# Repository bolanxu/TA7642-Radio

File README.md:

# TA7642 Radio

A very tiny pocket AM radio that runs from a single 1.5 V battery. It's a simple, low‑power receiver built around the TA7642 AM demodulator/amplifier IC with a small tuning coil and a coupling transistor to drive headphones. I designed this as a kit and created the PCB in 2021 (a 5th grade project) to learn about radios, basic electronics, and PCB design. More information in the `/docs` folder (The docs were written by me as a 5th grader, don't expect the best english 😅).

## Features
- Pocket‑sized AM radio
- Powered by a single 1.5 V cell (AA/AAA) or possibly a small 1.5V button battery
- TA7642 AM demodulator and amplifier IC
- Tuning via LC tank (coil + variable capacitor)
- Simple output amplifier transistor (Q1) for headphones/earbuds
- Designed as a kit with a compact PCB

## Circuit (overview)
- The LC tank (coil + capacitor) selects the desired AM frequency.  
- The TA7642 performs RF detection (demodulation) and provides a small amount of audio amplification.  
- A single transistor (Q1) follows the TA7642 to raise the audio level enough for headphones or small earbuds.  
- The schematic is shown above (`img/TA7642_radio_sch.png`)..

## Usage
1. Connect a fresh 1.5 V battery (observe polarity).
2. Plug headphones or earbuds into the audio jack or connect to the audio pads.
3. Slowly adjust the ferrite rod in the coil until you hear a station.
4. Fine‑tune the coil/trimmer for best reception and volume.

Note: This radio is optimized for strong local AM stations and will have limited sensitivity compared with larger receivers.

## Tuning and performance tips
- Use low‑impedance earbuds for better volume from the simple output stage.
- If reception is weak, try repositioning the coil or extending an earbud wire as an antenna.
- Small changes in the tuning capacitor or coil turns produce noticeable frequency shifts—tweak gently.
- The TA7642 and a single‑transistor buffer are designed for simplicity and low voltage operation; don't expect the same performance as higher‑powered receivers.

Enjoy building and listening, tiny radios are a great way to learn the fundamentals of RF and analog electronics!

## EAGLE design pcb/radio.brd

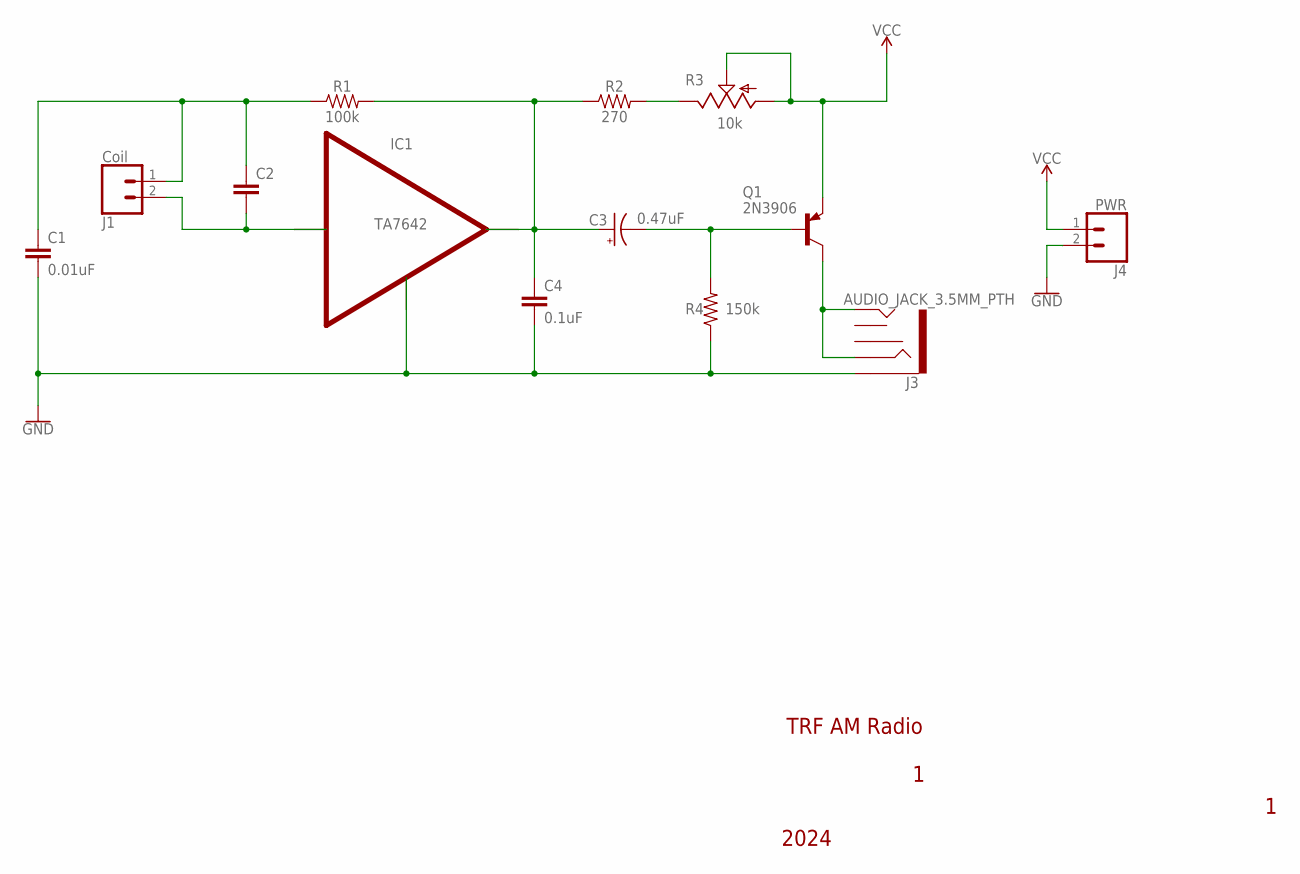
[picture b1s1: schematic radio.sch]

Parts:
C1: 0.01uF; CAP-PTH-2.54
C2: 22PF-PTH-2.54MM-200V-5%; CAP-PTH-2.54
C3: 0.47uF; CPOL-RADIAL-2.5MM-5MM
C4: 0.1uF; CAP-PTH-2.54
IC1: TA7642; TO92
J1: Coil; 1X02
J3: AUDIO_JACK_3.5MM_PTH; AUDIO-JACK
J4: PWR; 1X02
Q1: 2N3906; TO92
R1: 100k; AXIAL-0.3
R2: 270; AXIAL-0.3
R3: 10k; B25P
R4: 150k; AXIAL-0.3

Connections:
GND: C1.2, C4.2, IC1.2 (GND), J3.SLEEVE, J4.2, R4.P$1 (1)
unnamed: J3.RING, J3.TIP, Q1.1 (C)
unnamed: C3.1 (+), C4.1, IC1.1 (OUT), R1.P$2 (2), R2.P$1 (1)
unnamed: C1.1, C2.1, J1.1, R1.P$1 (1)
unnamed: R2.P$2 (2), R3.E
unnamed: C3.2 (-), Q1.2 (B), R4.P$2 (2)
unnamed: C2.2, IC1.3 (INPUT), J1.2
VCC: J4.1, Q1.3 (E), R3.A, R3.S

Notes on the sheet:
TRF AM Radio
2024

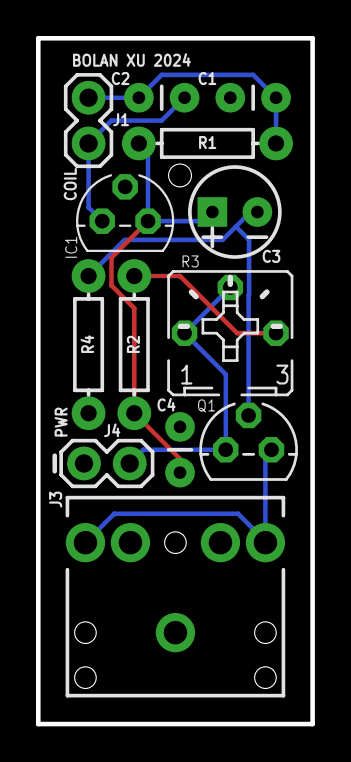
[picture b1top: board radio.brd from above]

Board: 2 copper layers, 15.2 x 38.1 mm, 13 parts (0 on the bottom side), 8 nets.

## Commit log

2025-11-02 Add circuit image to README
    Added an image of the radio circuit to the README.
2025-11-02 Enhance README with project details and instructions
    Expanded the description of the AM radio project and added features, circuit overview, usage instructions, and tuning tips.
2025-11-02 Update README with note on documentation quality
    Added a note about the documentation quality.

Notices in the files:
parts and their libraries:
SparkFun-Resistors: Licensing: Creative Commons ShareAlike 4.0 International - https://creativecommons.org/licenses/by-sa/4.0
